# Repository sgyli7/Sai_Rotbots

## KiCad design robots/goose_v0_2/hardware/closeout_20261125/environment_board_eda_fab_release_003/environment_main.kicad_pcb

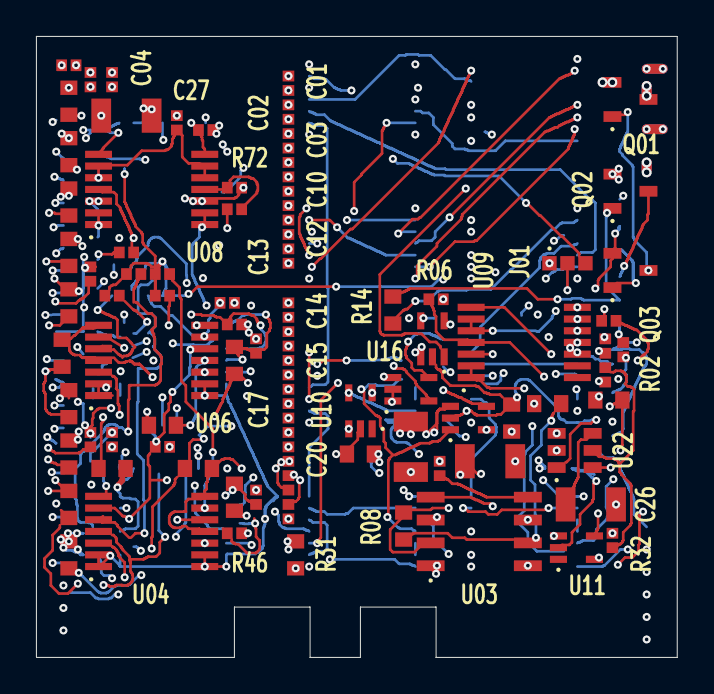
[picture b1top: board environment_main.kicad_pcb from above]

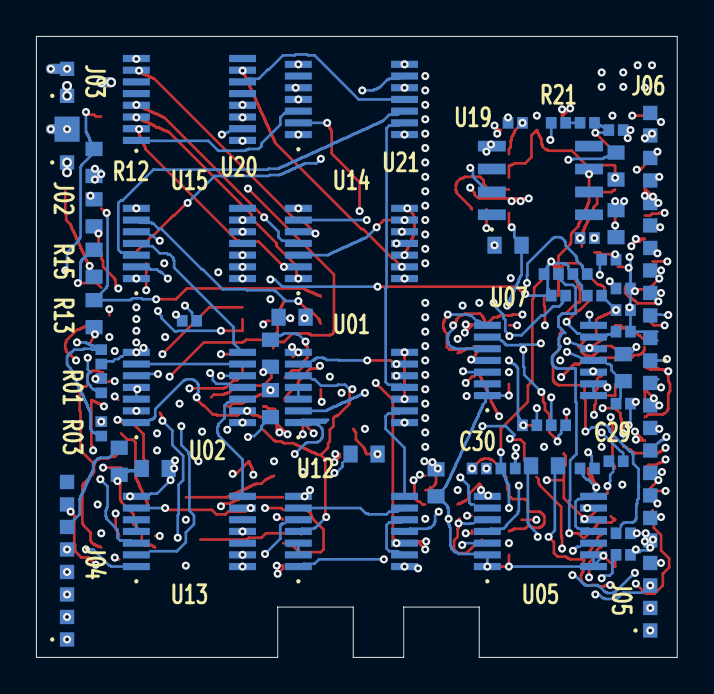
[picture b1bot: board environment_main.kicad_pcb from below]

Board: 6 copper layers, 35.6 x 34.5 mm, 142 parts (58 on the bottom side), 103 nets.

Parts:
C_D_U_E_AND1: GRM155R71C104KA88D; C_D_U_E_AND1
C_D_U_E_AND2: GRM155R71C104KA88D; C_D_U_E_AND2
C_D_U_E_CLOCK: GRM155R71C104KA88D; C_D_U_E_CLOCK
C_D_U_E_CMP1: GRM155R71C104KA88D; C_D_U_E_CMP1
C_D_U_E_CMP2: GRM155R71C104KA88D; C_D_U_E_CMP2
C_D_U_E_CMP3: GRM155R71C104KA88D; C_D_U_E_CMP3
C_D_U_E_CMP4: GRM155R71C104KA88D; C_D_U_E_CMP4
C_D_U_E_CMP5: GRM155R71C104KA88D; C_D_U_E_CMP5
C_D_U_E_CMP6: GRM155R71C104KA88D; C_D_U_E_CMP6
C_D_U_E_FAN_SERVICE_OK_BUF: GRM155R71C104KA88D; C_D_U_E_FAN_SERVICE_OK_BUF
C_D_U_E_FAN_TEST_ALLOW_BUF: GRM155R71C104KA88D; C_D_U_E_FAN_TEST_ALLOW_BUF
C_D_U_E_INV1: GRM155R71C104KA88D; C_D_U_E_INV1
C_D_U_E_INV2: GRM155R71C104KA88D; C_D_U_E_INV2
C_D_U_E_OR1: GRM155R71C104KA88D; C_D_U_E_OR1
C_D_U_E_OR2: GRM155R71C104KA88D; C_D_U_E_OR2
C_D_U_E_OUT_FAN: GRM155R71C104KA88D; C_D_U_E_OUT_FAN
C_D_U_E_OUT_PWR: GRM155R71C104KA88D; C_D_U_E_OUT_PWR
C_D_U_E_OUT_TEMP: GRM155R71C104KA88D; C_D_U_E_OUT_TEMP
C_D_U_E_REF: GRM155R71C104KA88D; C_D_U_E_REF
C_D_U_E_SEQ: GRM155R71C104KA88D; C_D_U_E_SEQ
C_D_U_E_STATE: GRM155R71C104KA88D; C_D_U_E_STATE
C_D_U_E_SUP: GRM155R71C104KA88D; C_D_U_E_SUP
C_E_BULK: GRM31CR72A105KA01L; C_E_BULK
C_E_CLOCK: GRM31CR72A105KA01L; C_E_CLOCK
C_E_CLOCK_CTRL: GRM155R71C104KA88D; C_E_CLOCK_CTRL
C_E_CT: C3216X7R2A224K115AA; C_E_CT
C_E_DP_FILT: GRM155R71C104KA88D; C_E_DP_FILT
C_E_REF: GRM31CR72A105KA01L; C_E_REF
C_E_T0_FILTER: GRM155R71C104KA88D; C_E_T0_FILTER
C_E_T1_FILTER: GRM155R71C104KA88D; C_E_T1_FILTER
C_E_T2_FILTER: GRM155R71C104KA88D; C_E_T2_FILTER
C_E_T3_FILTER: GRM155R71C104KA88D; C_E_T3_FILTER
C_E_T4_FILTER: GRM155R71C104KA88D; C_E_T4_FILTER
C_E_T5_FILTER: GRM155R71C104KA88D; C_E_T5_FILTER
C_E_T6_FILTER: GRM155R71C104KA88D; C_E_T6_FILTER
C_E_T7_FILTER: GRM155R71C104KA88D; C_E_T7_FILTER
J_ENV_DP: J_ENV_DP
J_ENV_FAN_IN: J_ENV_FAN_IN
J_ENV_FAN_OUT: J_ENV_FAN_OUT
J_ENV_HOST: J_ENV_HOST
J_ENV_PROBES_A: J_ENV_PROBES_A
J_ENV_PROBES_B: J_ENV_PROBES_B
Q_E_FAN: AO3407A; Q_E_FAN
Q_E_FAN_OFF_N: MMBT3904LT1G; Q_E_FAN_OFF_N
Q_E_FAN_OFF_P: MMBT3906LT1G; Q_E_FAN_OFF_P
R_E_12_OV_A: TNPU040210K7HZEP00; R_E_12_OV_A
R_E_12_OV_B: TNPU040210K0HZEP00; R_E_12_OV_B
R_E_12_SENSE_A: TNPU0402100KHZEP00; R_E_12_SENSE_A
R_E_12_SENSE_B: TNPU040210K0HZEP00; R_E_12_SENSE_B
R_E_12_UV_A: TNPU040216K2HZEP00; R_E_12_UV_A
R_E_12_UV_B: TNPU040210K0HZEP00; R_E_12_UV_B
R_E_CLOCK_A: RC0603FR-07100KL; R_E_CLOCK_A
R_E_CLOCK_B: RC0603FR-07316KL; R_E_CLOCK_B
R_E_DP_FILT: RC0603FR-0710KL; R_E_DP_FILT
R_E_DP_PD: RC0603FR-07100KL; R_E_DP_PD
R_E_FAN12_PU: RC0603FR-0710KL; R_E_FAN12_PU
R_E_FAN_GATE_PD: RC0603FR-0747KL; R_E_FAN_GATE_PD
R_E_FAN_OFF_BE: RC0603FR-07100KL; R_E_FAN_OFF_BE
R_E_FAN_OFF_NB: RC0603FR-0722KL; R_E_FAN_OFF_NB
R_E_FAN_OFF_PB: RC0603FR-0710KL; R_E_FAN_OFF_PB
R_E_FAN_OFF_PE: RC0603FR-07100KL; R_E_FAN_OFF_PE
R_E_FAN_SERVICE_OK_IN: RC0603FR-0710KL; R_E_FAN_SERVICE_OK_IN
R_E_FAN_SERVICE_OK_PD: RC0603FR-07100KL; R_E_FAN_SERVICE_OK_PD
R_E_FAN_TEST_ALLOW_IN: RC0603FR-0710KL; R_E_FAN_TEST_ALLOW_IN
R_E_FAN_TEST_ALLOW_PD: RC0603FR-07100KL; R_E_FAN_TEST_ALLOW_PD
R_E_FLOW_HI_A: TNPU040220K5HZEP00; R_E_FLOW_HI_A
R_E_FLOW_HI_B: TNPU0402147RHZEP00; R_E_FLOW_HI_B
R_E_FLOW_HI_G: TNPU040210K0HZEP00; R_E_FLOW_HI_G
R_E_FLOW_LO_A: TNPU040229K4HZEP00; R_E_FLOW_LO_A
R_E_FLOW_LO_B: TNPU0402182RHZEP00; R_E_FLOW_LO_B
R_E_FLOW_LO_G: TNPU040210K0HZEP00; R_E_FLOW_LO_G
R_E_FLOW_PU: RC0603FR-0710KL; R_E_FLOW_PU
R_E_OUT_FAN: RC0603FR-071KL; R_E_OUT_FAN
R_E_OUT_PWR: RC0603FR-071KL; R_E_OUT_PWR
R_E_OUT_TEMP: RC0603FR-071KL; R_E_OUT_TEMP
R_E_RAIL_BLEED: RC0603FR-0710KL; R_E_RAIL_BLEED
R_E_SUP_BOT: TNPU040210K0HZEP00; R_E_SUP_BOT
R_E_SUP_PU: RC0603FR-0710KL; R_E_SUP_PU
R_E_SUP_TOP_A: TNPU0402100KHZEP00; R_E_SUP_TOP_A
R_E_SUP_TOP_B: TNPU04021K00HZEP00; R_E_SUP_TOP_B
R_E_T0_FILTER: RC0603FR-071KL; R_E_T0_FILTER
R_E_T0_HI: TNPU040214K3HZEP00; R_E_T0_HI
R_E_T0_LO: TNPU04029K76HZEP00; R_E_T0_LO
R_E_T0_PD: RC0603FR-07100KL; R_E_T0_PD
R_E_T1_FILTER: RC0603FR-071KL; R_E_T1_FILTER
R_E_T1_HI: TNPU040214K3HZEP00; R_E_T1_HI
R_E_T1_LO: TNPU04029K76HZEP00; R_E_T1_LO
R_E_T1_PD: RC0603FR-07100KL; R_E_T1_PD
R_E_T2_FILTER: RC0603FR-071KL; R_E_T2_FILTER
R_E_T2_HI: TNPU040214K3HZEP00; R_E_T2_HI
R_E_T2_LO: TNPU04029K76HZEP00; R_E_T2_LO
R_E_T2_PD: RC0603FR-07100KL; R_E_T2_PD
R_E_T3_FILTER: RC0603FR-071KL; R_E_T3_FILTER
R_E_T3_HI: TNPU040214K3HZEP00; R_E_T3_HI
R_E_T3_LO: TNPU04029K76HZEP00; R_E_T3_LO
R_E_T3_PD: RC0603FR-07100KL; R_E_T3_PD
R_E_T4_FILTER: RC0603FR-071KL; R_E_T4_FILTER
R_E_T4_HI: TNPU040214K3HZEP00; R_E_T4_HI
R_E_T4_LO: TNPU04029K76HZEP00; R_E_T4_LO
R_E_T4_PD: RC0603FR-07100KL; R_E_T4_PD
R_E_T5_FILTER: RC0603FR-071KL; R_E_T5_FILTER
R_E_T5_HI: TNPU040214K3HZEP00; R_E_T5_HI
R_E_T5_LO: TNPU04029K76HZEP00; R_E_T5_LO
R_E_T5_PD: RC0603FR-07100KL; R_E_T5_PD
R_E_T6_FILTER: RC0603FR-071KL; R_E_T6_FILTER
R_E_T6_HI: TNPU040214K3HZEP00; R_E_T6_HI
R_E_T6_LO: TNPU04029K76HZEP00; R_E_T6_LO
R_E_T6_PD: RC0603FR-07100KL; R_E_T6_PD
R_E_T7_FILTER: RC0603FR-071KL; R_E_T7_FILTER
R_E_T7_HI: TNPU040214K3HZEP00; R_E_T7_HI
R_E_T7_LO: TNPU04029K76HZEP00; R_E_T7_LO
R_E_T7_PD: RC0603FR-07100KL; R_E_T7_PD
R_E_TEMP_PU: RC0603FR-0710KL; R_E_TEMP_PU
R_E_TLOW_A: TNPU040253K6HZEP00; R_E_TLOW_A
R_E_TLOW_B: TNPU040210K0HZEP00; R_E_TLOW_B
R_E_ZERO_HI_A: TNPU040238K1HZEP00; R_E_ZERO_HI_A
R_E_ZERO_HI_G: TNPU040210K0HZEP00; R_E_ZERO_HI_G
R_E_ZERO_LO_A: TNPU040242K2HZEP00; R_E_ZERO_LO_A
R_E_ZERO_LO_G: TNPU040210K0HZEP00; R_E_ZERO_LO_G
R_E_ZERO_PU: RC0603FR-0710KL; R_E_ZERO_PU
U_E_AND1: SN74HC08PWR; U_E_AND1
U_E_AND2: SN74HC08PWR; U_E_AND2
U_E_CLOCK: TLC555IDR; U_E_CLOCK
U_E_CMP1: LM339BIPWR; U_E_CMP1
U_E_CMP2: LM339BIPWR; U_E_CMP2
U_E_CMP3: LM339BIPWR; U_E_CMP3
U_E_CMP4: LM339BIPWR; U_E_CMP4
U_E_CMP5: LM339BIPWR; U_E_CMP5
U_E_CMP6: LM339BIPWR; U_E_CMP6
U_E_FAN_SERVICE_OK_BUF: SN74LVC1G17DCKR; U_E_FAN_SERVICE_OK_BUF
U_E_FAN_TEST_ALLOW_BUF: SN74LVC1G17DCKR; U_E_FAN_TEST_ALLOW_BUF
U_E_INV1: SN74HC14PWR; U_E_INV1
U_E_INV2: SN74HC14PWR; U_E_INV2
U_E_OR1: SN74HC32PWR; U_E_OR1
U_E_OR2: SN74HC32PWR; U_E_OR2
U_E_OUT_FAN: SN74LVC1G08DCKR; U_E_OUT_FAN
U_E_OUT_PWR: SN74LVC1G08DCKR; U_E_OUT_PWR
U_E_OUT_TEMP: SN74LVC1G08DCKR; U_E_OUT_TEMP
U_E_REF: REF5025IDR; U_E_REF
U_E_SEQ: CD74HC4017PWR; U_E_SEQ
U_E_STATE: SN74HC74PWR; U_E_STATE
U_E_SUP: TPS3808G01DBVR; U_E_SUP

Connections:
ENV_PWR_OK: J_ENV_HOST.5, R_E_OUT_PWR.2
ENV_V5: C_D_U_E_AND1.1, C_D_U_E_AND2.1, C_D_U_E_CLOCK.1, C_D_U_E_CMP1.1, C_D_U_E_CMP2.1, C_D_U_E_CMP3.1, C_D_U_E_CMP4.1, C_D_U_E_CMP5.1, C_D_U_E_CMP6.1, C_D_U_E_FAN_SERVICE_OK_BUF.1, C_D_U_E_FAN_TEST_ALLOW_BUF.1, C_D_U_E_INV1.1, C_D_U_E_INV2.1, C_D_U_E_OR1.1, C_D_U_E_OR2.1, C_D_U_E_OUT_FAN.1, C_D_U_E_OUT_PWR.1, C_D_U_E_OUT_TEMP.1, C_D_U_E_REF.1, C_D_U_E_SEQ.1, C_D_U_E_STATE.1, C_D_U_E_SUP.1, C_E_BULK.1, J_ENV_DP.1, J_ENV_HOST.1, J_ENV_PROBES_A.1, J_ENV_PROBES_A.4, J_ENV_PROBES_A.7, J_ENV_PROBES_A.10, J_ENV_PROBES_B.1, J_ENV_PROBES_B.4, J_ENV_PROBES_B.7, J_ENV_PROBES_B.10, R_E_CLOCK_A.1, R_E_FAN12_PU.1, R_E_FLOW_HI_A.1, R_E_FLOW_LO_A.1, R_E_FLOW_PU.1, R_E_RAIL_BLEED.1, R_E_SUP_PU.1, R_E_SUP_TOP_A.1, R_E_TEMP_PU.1, R_E_ZERO_HI_A.1, R_E_ZERO_LO_A.1, R_E_ZERO_PU.1, U_E_AND1.14, U_E_AND2.14, U_E_CLOCK.8, U_E_CMP1.3, U_E_CMP2.3, U_E_CMP3.3, U_E_CMP4.3, U_E_CMP5.3, U_E_CMP6.3, U_E_FAN_SERVICE_OK_BUF.5, U_E_FAN_TEST_ALLOW_BUF.5, U_E_INV1.14, U_E_INV2.14, U_E_OR1.14, U_E_OR2.14, U_E_OUT_FAN.5, U_E_OUT_PWR.5, U_E_OUT_TEMP.5, U_E_REF.2, U_E_SEQ.16, U_E_STATE.4, U_E_STATE.10, U_E_STATE.14, U_E_SUP.3, U_E_SUP.6
E_12_OV: R_E_12_OV_A.2, R_E_12_OV_B.1, U_E_CMP6.7
E_12_SENSE: R_E_12_SENSE_A.2, R_E_12_SENSE_B.1, U_E_CMP6.5, U_E_CMP6.6
E_12_UV: R_E_12_UV_A.2, R_E_12_UV_B.1, U_E_CMP6.4
E_ALL_POWER_TEMP: U_E_AND1.8, U_E_AND1.12
E_CAN_OFF: U_E_AND2.6, U_E_AND2.9
E_CLK: U_E_CLOCK.3, U_E_SEQ.14
E_CLOCK_C: C_E_CLOCK.1, R_E_CLOCK_B.2, U_E_CLOCK.2, U_E_CLOCK.6
E_CLOCK_CTRL: C_E_CLOCK_CTRL.1, U_E_CLOCK.5
E_CLOCK_DIS: R_E_CLOCK_A.2, R_E_CLOCK_B.1, U_E_CLOCK.7
E_CT: C_E_CT.1, U_E_SUP.4
E_DP_AOUT: J_ENV_DP.3, R_E_DP_FILT.1, R_E_DP_PD.1
E_DP_S: C_E_DP_FILT.1, R_E_DP_FILT.2, U_E_CMP5.5, U_E_CMP5.6, U_E_CMP5.9, U_E_CMP5.10
E_FAN12_BAD: U_E_AND2.12, U_E_INV2.8
E_FAN12_N: U_E_INV2.4, U_E_INV2.5
E_FAN12_OC: R_E_FAN12_PU.2, U_E_CMP6.1, U_E_CMP6.2, U_E_INV2.3
E_FAN12_RAW: U_E_AND1.10, U_E_INV2.6, U_E_INV2.9
E_FAN_DRIVE: R_E_OUT_FAN.1, U_E_OUT_FAN.4
E_FAN_GATE: Q_E_FAN.1, Q_E_FAN_OFF_P.3, R_E_FAN_GATE_PD.1
E_FAN_OFF_C: Q_E_FAN_OFF_N.3, R_E_FAN_OFF_PB.2
E_FAN_OFF_CMD: U_E_AND2.8, U_E_OR2.4
E_FAN_OFF_EFFECTIVE: R_E_FAN_OFF_NB.1, U_E_OR2.6
E_FAN_OFF_NB: Q_E_FAN_OFF_N.1, R_E_FAN_OFF_BE.1, R_E_FAN_OFF_NB.2
E_FAN_OFF_PB: Q_E_FAN_OFF_P.1, R_E_FAN_OFF_PB.1, R_E_FAN_OFF_PE.1
E_FAN_POWER_BAD: U_E_AND2.11, U_E_OR2.5
E_FAN_SERVICE_OK: U_E_AND1.2, U_E_FAN_SERVICE_OK_BUF.4
E_FAN_SERVICE_OK_PIN: R_E_FAN_SERVICE_OK_IN.2, R_E_FAN_SERVICE_OK_PD.1, U_E_FAN_SERVICE_OK_BUF.2
E_FAN_TEST_ALLOW: U_E_AND2.2, U_E_FAN_TEST_ALLOW_BUF.4
E_FAN_TEST_ALLOW_PIN: R_E_FAN_TEST_ALLOW_IN.2, R_E_FAN_TEST_ALLOW_PD.1, U_E_FAN_TEST_ALLOW_BUF.2
E_FLOW_CLR_N: U_E_AND1.11, U_E_STATE.13
E_FLOW_D: U_E_OR2.3, U_E_STATE.12
E_FLOW_HI: R_E_FLOW_HI_B.2, R_E_FLOW_HI_G.1, U_E_CMP5.7
E_FLOW_HI_MID: R_E_FLOW_HI_A.2, R_E_FLOW_HI_B.1
E_FLOW_LO: R_E_FLOW_LO_B.2, R_E_FLOW_LO_G.1, U_E_CMP5.4
E_FLOW_LO_MID: R_E_FLOW_LO_A.2, R_E_FLOW_LO_B.1
E_FLOW_N: U_E_INV1.6, U_E_INV1.9
E_FLOW_OC: R_E_FLOW_PU.2, U_E_CMP5.1, U_E_CMP5.2, U_E_INV1.5
E_FLOW_PASS: U_E_OR2.2, U_E_OUT_FAN.1, U_E_STATE.9
E_FLOW_PASS_N: U_E_AND2.5, U_E_STATE.8
E_FLOW_RAW: U_E_AND1.13, U_E_INV1.8
E_HOST_GOOD: U_E_AND1.3, U_E_AND1.4
E_HOST_TEMP: U_E_AND1.6, U_E_AND1.9
E_OFF_PHASE: U_E_AND2.10, U_E_OR1.11
E_PWR_BAD: U_E_INV2.2, U_E_SEQ.15
E_PWR_DRIVE: R_E_OUT_PWR.1, U_E_OUT_PWR.4
E_PWR_RAW: R_E_SUP_PU.2, U_E_AND1.1, U_E_AND2.1, U_E_AND2.13, U_E_CLOCK.4, U_E_INV2.1, U_E_OUT_FAN.2, U_E_OUT_PWR.1, U_E_OUT_PWR.2, U_E_OUT_TEMP.2, U_E_SUP.1
E_Q0: U_E_OR1.1, U_E_SEQ.3
E_Q1: U_E_OR1.2, U_E_SEQ.2
E_Q01: U_E_OR1.3, U_E_OR1.9
E_Q2: U_E_OR1.4, U_E_SEQ.4
E_Q3: U_E_OR1.5, U_E_SEQ.7
E_Q03: U_E_OR1.8, U_E_OR1.12
E_Q4: U_E_OR1.13, U_E_SEQ.10
E_Q5: U_E_SEQ.1, U_E_STATE.3
E_Q9: U_E_SEQ.11, U_E_STATE.11
E_Q23: U_E_OR1.6, U_E_OR1.10
E_REF25: C_E_REF.1, R_E_12_OV_A.1, R_E_12_UV_A.1, R_E_T0_HI.1, R_E_T1_HI.1, R_E_T2_HI.1, R_E_T3_HI.1, R_E_T4_HI.1, R_E_T5_HI.1, R_E_T6_HI.1, R_E_T7_HI.1, R_E_TLOW_A.1, U_E_REF.6
E_SUP_TOP: R_E_SUP_TOP_A.2, R_E_SUP_TOP_B.1
E_T0_LIMIT: R_E_T0_HI.2, R_E_T0_LO.1, U_E_CMP1.5
E_T0_S: C_E_T0_FILTER.1, R_E_T0_FILTER.2, U_E_CMP1.4, U_E_CMP1.7
E_T1_LIMIT: R_E_T1_HI.2, R_E_T1_LO.1, U_E_CMP1.9
E_T1_S: C_E_T1_FILTER.1, R_E_T1_FILTER.2, U_E_CMP1.8, U_E_CMP1.11
E_T2_LIMIT: R_E_T2_HI.2, R_E_T2_LO.1, U_E_CMP2.5
E_T2_S: C_E_T2_FILTER.1, R_E_T2_FILTER.2, U_E_CMP2.4, U_E_CMP2.7
E_T3_LIMIT: R_E_T3_HI.2, R_E_T3_LO.1, U_E_CMP2.9
E_T3_S: C_E_T3_FILTER.1, R_E_T3_FILTER.2, U_E_CMP2.8, U_E_CMP2.11
E_T4_LIMIT: R_E_T4_HI.2, R_E_T4_LO.1, U_E_CMP3.5
E_T4_S: C_E_T4_FILTER.1, R_E_T4_FILTER.2, U_E_CMP3.4, U_E_CMP3.7
E_T5_LIMIT: R_E_T5_HI.2, R_E_T5_LO.1, U_E_CMP3.9
E_T5_S: C_E_T5_FILTER.1, R_E_T5_FILTER.2, U_E_CMP3.8, U_E_CMP3.11
E_T6_LIMIT: R_E_T6_HI.2, R_E_T6_LO.1, U_E_CMP4.5
E_T6_S: C_E_T6_FILTER.1, R_E_T6_FILTER.2, U_E_CMP4.4, U_E_CMP4.7
E_T7_LIMIT: R_E_T7_HI.2, R_E_T7_LO.1, U_E_CMP4.9
E_T7_S: C_E_T7_FILTER.1, R_E_T7_FILTER.2, U_E_CMP4.8, U_E_CMP4.11
E_TEMP_DRIVE: R_E_OUT_TEMP.1, U_E_OUT_TEMP.4
E_TEMP_N: U_E_INV1.2, U_E_INV1.3
E_TEMP_OC: R_E_TEMP_PU.2, U_E_CMP1.1, U_E_CMP1.2, U_E_CMP1.13, U_E_CMP1.14, U_E_CMP2.1, U_E_CMP2.2, U_E_CMP2.13, U_E_CMP2.14, U_E_CMP3.1, U_E_CMP3.2, U_E_CMP3.13, U_E_CMP3.14, U_E_CMP4.1, U_E_CMP4.2, U_E_CMP4.13, U_E_CMP4.14, U_E_INV1.1
E_TEMP_RAW: U_E_AND1.5, U_E_INV1.4, U_E_OUT_TEMP.1
E_T_LOW: R_E_TLOW_A.2, R_E_TLOW_B.1, U_E_CMP1.6, U_E_CMP1.10, U_E_CMP2.6, U_E_CMP2.10, U_E_CMP3.6, U_E_CMP3.10, U_E_CMP4.6, U_E_CMP4.10
E_V5_SENSE: R_E_SUP_BOT.1, R_E_SUP_TOP_B.2, U_E_SUP.5
E_ZERO_CLR_N: U_E_AND2.3, U_E_AND2.4, U_E_STATE.1
E_ZERO_HI: R_E_ZERO_HI_A.2, R_E_ZERO_HI_G.1, U_E_CMP5.11
E_ZERO_LO: R_E_ZERO_LO_A.2, R_E_ZERO_LO_G.1, U_E_CMP5.8
E_ZERO_N: U_E_INV1.10, U_E_INV1.13
E_ZERO_OC: R_E_ZERO_PU.2, U_E_CMP5.13, U_E_CMP5.14, U_E_INV1.11
E_ZERO_PASS: U_E_OR2.1, U_E_STATE.5
E_ZERO_RAW: U_E_INV1.12, U_E_STATE.2
FAN12_IN: J_ENV_FAN_IN.1, Q_E_FAN.2, Q_E_FAN_OFF_P.2, R_E_12_SENSE_A.1, R_E_FAN_OFF_PE.2
FAN12_OUT: J_ENV_FAN_OUT.1, Q_E_FAN.3
FAN_OK: J_ENV_HOST.4, R_E_OUT_FAN.2
FAN_SERVICE_OK: J_ENV_HOST.7, R_E_FAN_SERVICE_OK_IN.1
FAN_TEST_ALLOW: J_ENV_HOST.6, R_E_FAN_TEST_ALLOW_IN.1
GND: C_D_U_E_AND1.2, C_D_U_E_AND2.2, C_D_U_E_CLOCK.2, C_D_U_E_CMP1.2, C_D_U_E_CMP2.2, C_D_U_E_CMP3.2, C_D_U_E_CMP4.2, C_D_U_E_CMP5.2, C_D_U_E_CMP6.2, C_D_U_E_FAN_SERVICE_OK_BUF.2, C_D_U_E_FAN_TEST_ALLOW_BUF.2, C_D_U_E_INV1.2, C_D_U_E_INV2.2, C_D_U_E_OR1.2, C_D_U_E_OR2.2, C_D_U_E_OUT_FAN.2, C_D_U_E_OUT_PWR.2, C_D_U_E_OUT_TEMP.2, C_D_U_E_REF.2, C_D_U_E_SEQ.2, C_D_U_E_STATE.2, C_D_U_E_SUP.2, C_E_BULK.2, C_E_CLOCK.2, C_E_CLOCK_CTRL.2, C_E_CT.2, C_E_DP_FILT.2, C_E_REF.2, C_E_T0_FILTER.2, C_E_T1_FILTER.2, C_E_T2_FILTER.2, C_E_T3_FILTER.2, C_E_T4_FILTER.2, C_E_T5_FILTER.2, C_E_T6_FILTER.2, C_E_T7_FILTER.2, J_ENV_DP.2, J_ENV_FAN_IN.2, J_ENV_FAN_OUT.2, J_ENV_HOST.2, J_ENV_PROBES_A.2, J_ENV_PROBES_A.5, J_ENV_PROBES_A.8, J_ENV_PROBES_A.11, J_ENV_PROBES_B.2, J_ENV_PROBES_B.5, J_ENV_PROBES_B.8, J_ENV_PROBES_B.11, Q_E_FAN_OFF_N.2, R_E_12_OV_B.2, R_E_12_SENSE_B.2, R_E_12_UV_B.2, R_E_DP_PD.2, R_E_FAN_GATE_PD.2, R_E_FAN_OFF_BE.2, R_E_FAN_SERVICE_OK_PD.2, R_E_FAN_TEST_ALLOW_PD.2, R_E_FLOW_HI_G.2, R_E_FLOW_LO_G.2, R_E_RAIL_BLEED.2, R_E_SUP_BOT.2, R_E_T0_LO.2, R_E_T0_PD.2, R_E_T1_LO.2, R_E_T1_PD.2, R_E_T2_LO.2, R_E_T2_PD.2, R_E_T3_LO.2, R_E_T3_PD.2, R_E_T4_LO.2, R_E_T4_PD.2, R_E_T5_LO.2, R_E_T5_PD.2, R_E_T6_LO.2, R_E_T6_PD.2, R_E_T7_LO.2, R_E_T7_PD.2, R_E_TLOW_B.2, R_E_ZERO_HI_G.2, R_E_ZERO_LO_G.2, U_E_AND1.7, U_E_AND2.7, U_E_CLOCK.1, U_E_CMP1.12, U_E_CMP2.12, U_E_CMP3.12, U_E_CMP4.12, U_E_CMP5.12, U_E_CMP6.8, U_E_CMP6.9, U_E_CMP6.10, U_E_CMP6.11, U_E_CMP6.12, U_E_FAN_SERVICE_OK_BUF.3, U_E_FAN_TEST_ALLOW_BUF.3, U_E_INV1.7, U_E_INV2.7, U_E_INV2.11, U_E_INV2.13, U_E_OR1.7, U_E_OR2.7, U_E_OR2.9, U_E_OR2.10, U_E_OR2.12, U_E_OR2.13, U_E_OUT_FAN.3, U_E_OUT_PWR.3, U_E_OUT_TEMP.3, U_E_REF.4, U_E_SEQ.8, U_E_SEQ.13, U_E_STATE.7, U_E_SUP.2
TEMP_0: J_ENV_PROBES_A.3, R_E_T0_FILTER.1, R_E_T0_PD.1
TEMP_1: J_ENV_PROBES_A.6, R_E_T1_FILTER.1, R_E_T1_PD.1
TEMP_2: J_ENV_PROBES_A.9, R_E_T2_FILTER.1, R_E_T2_PD.1
TEMP_3: J_ENV_PROBES_A.12, R_E_T3_FILTER.1, R_E_T3_PD.1
TEMP_4: J_ENV_PROBES_B.3, R_E_T4_FILTER.1, R_E_T4_PD.1
TEMP_5: J_ENV_PROBES_B.6, R_E_T5_FILTER.1, R_E_T5_PD.1
TEMP_6: J_ENV_PROBES_B.9, R_E_T6_FILTER.1, R_E_T6_PD.1
TEMP_7: J_ENV_PROBES_B.12, R_E_T7_FILTER.1, R_E_T7_PD.1
TEMP_OK: J_ENV_HOST.3, R_E_OUT_TEMP.2
